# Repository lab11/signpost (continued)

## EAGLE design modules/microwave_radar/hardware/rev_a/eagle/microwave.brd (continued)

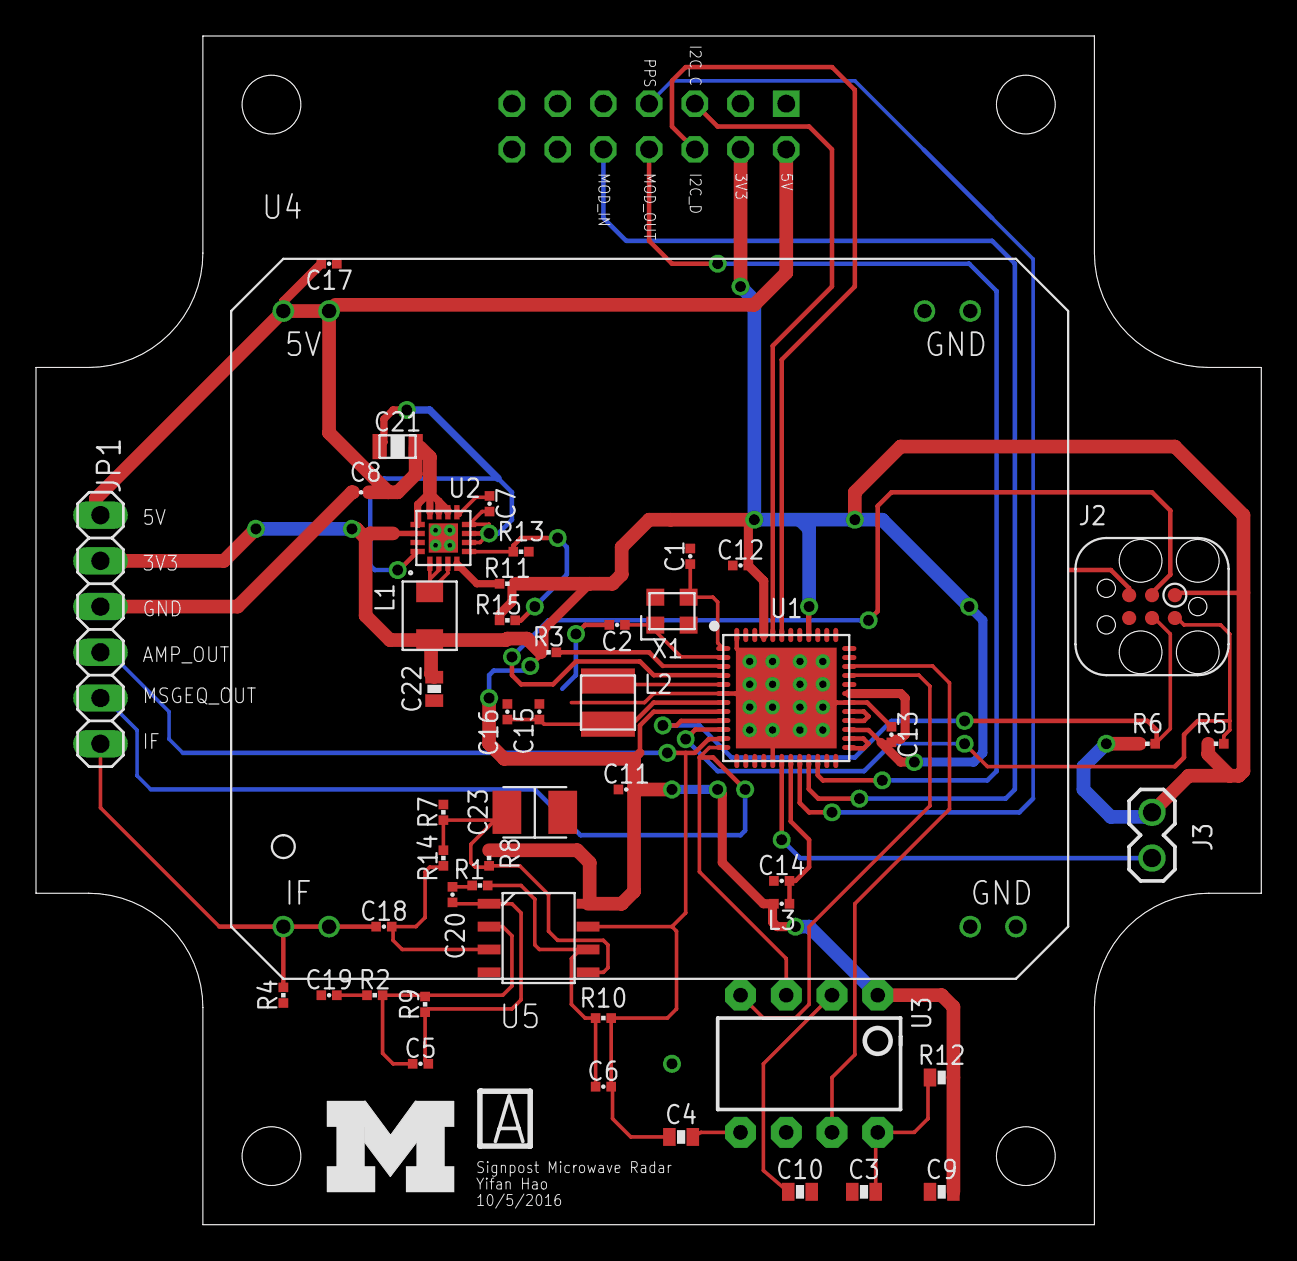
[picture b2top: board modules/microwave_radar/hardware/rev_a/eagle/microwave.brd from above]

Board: 2 copper layers, 68.1 x 66.0 mm, 52 parts (0 on the bottom side), 39 nets.

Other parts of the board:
U$1: UMICH_SOLID_200MIL

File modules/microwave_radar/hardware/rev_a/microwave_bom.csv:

"Qty";"Value";"Device";"Package";"Parts";"Description";"DIGIKEY";
"1";"";"FH1600015";"FHXXX";"X1";"Pericom Type FH 16 MHz 2.5 x 2.0 mm";"FH1600015CT-ND";
"1";"";"JUMPER-2PTH";"1X02";"J3";"Jumper";"";
"1";"";"PINHD-1X8";"1X08";"JP2";"PIN HEADER";"";
"1";"0.1uF";"CAPACITOR0402_CAP";"0402_CAP";"C8";"0402 Capacitor";"490-5920-1-ND";
"2";"0.1uF";"CAPACITOR0603_CAP";"0603_CAP";"C9, C10";"0402 Capacitor";"490-1532-1-ND";
"1";"1.5k";"FERRITE_BEAD0402";"0402_CAP";"L3";"";"490-5216-1-ND";
"6";"100k";"RESISTOR0402_RES";"0402_RES";"R7, R8, R9, R10, R11, R12";"Resistor";"1276-3432-1-ND";
"1";"100k";"RESISTOR0402_RES";"0402_RES";"R13";"Resistor";"P100KJCT-ND";
"6";"100nF";"CAPACITOR0402_CAP";"0402_CAP";"C11, C12, C13, C14, C16, C17";"0402 Capacitor";"490-10777-1-ND";
"1";"100nF";"CAPACITOR0402_CAP";"0402_CAP";"C15";"0402 Capacitor";"490-13252-1-ND";
"1";"100uF";"CAPACITOR1210_CAP";"1210_CAP";"C23";"0402 Capacitor";"490-3390-1-ND";
"2";"10k";"RESISTOR0402_RES";"0402_RES";"R4, R5";"Resistor";"1276-3431-1-ND";
"1";"10uF";"CAPACITOR0805_CAP";"0805_CAP";"C21";"0402 Capacitor";"490-5523-1-ND";
"1";"12k";"RESISTOR0402_RES";"0402_RES";"R6";"Resistor";"1276-4122-1-ND";
"2";"1k";"RESISTOR0402_RES";"0402_RES";"R1, R2";"Resistor";"1276-3430-1-ND";
"1";"1nF";"CAPACITOR0603_CAP";"0603_CAP";"C4";"0402 Capacitor";"490-1494-1-ND";
"2";"2.2nF";"CAPACITOR0402_CAP";"0402_CAP";"C5, C6";"0402 Capacitor";"490-11418-1-ND";
"1";"2.2uH";"INDUCTORIHL";"IHL-1212BZ-11";"L1";"A very specific inductor";"541-1322-1-ND";
"1";"200k";"RESISTOR0603_RES";"0603-RES";"R14";"Resistor";"RHM200KCFCT-ND";
"1";"22uF";"CAPACITOR0603_CAP";"0603_CAP";"C22";"0402 Capacitor";"1276-1193-1-ND";
"1";"22uH";"LHQ3NP";"1212";"L2";"LHQ3NP Inductor";"490-5350-1-ND";
"1";"240k";"RESISTOR0402_RES";"0402_RES";"R15";"Resistor";"P240KLCT-ND";
"1";"3.3nF";"CAPACITOR0402_CAP";"0402_CAP";"C7";"0402 Capacitor";"490-3248-1-ND";
"1";"330k";"RESISTOR0402_RES";"0402_RES";"R16";"Resistor";"1276-4244-1-ND";
"1";"33pF";"CAPACITOR0603_CAP";"0603_CAP";"C3";"0402 Capacitor";"490-1415-1-ND";
"3";"4.7uF";"CAPACITOR0402_CAP";"0402_CAP";"C18, C19, C20";"0402 Capacitor";"1276-1481-1-ND";
"1";"750k";"RESISTOR0402_RES";"0402_RES";"R17";"Resistor";"P750KLCT-ND";
"1";"8.2k";"RESISTOR0402_RES";"0402_RES";"R3";"Resistor";"311-8.20KLRCT-ND";
"2";"8pF";"CAPACITOR0402_CAP";"0402_CAP";"C1, C2";"0402 Capacitor";"490-8230-1-ND";
"1";"HB100";"HB100";"HB100";"U4";"";"SAM1067-02-ND";
"2";"LED0603";"LED0603";"LED-0603";"LED1, LED2";"LED";"";
"1";"MODULE_GENERIC";"MODULE_GENERIC";"MODULE_GENERIC";"J1";"Module header and PCB  guildes for signposts";"S9170-ND";
"1";"MSGEQ7";"MSGEQ7";"DIP-8";"U3";"A CMOS spectrum analyzer";"1568-1335-ND";
"1";"OP284E_SEPARATE";"OP284E_SEPARATE";"OP284E_SEPARATE";"U5";"";"OP284ESZ-ND";
"1";"SAM4LC8AA";"SAM4LC8AA";"QFN-48-7MM";"U1";"Atmel SAM4L microcontroller. ARM Cortex M4 with 512 KB Flash and 64 KB RAM";"ATSAM4LC8AA-MU-ND";
"1";"TC2030-JLINK-L";"TC2030-JLINK-L";"TC2030-IDC";"J2";"";"";
"1";"TLV62130";"TLV62130";"TQFN-16/3MM";"U2";"High Efficient 3A switching step-down regulator. 1V-5V out, 4V-17V in.";"296-35978-1-ND";

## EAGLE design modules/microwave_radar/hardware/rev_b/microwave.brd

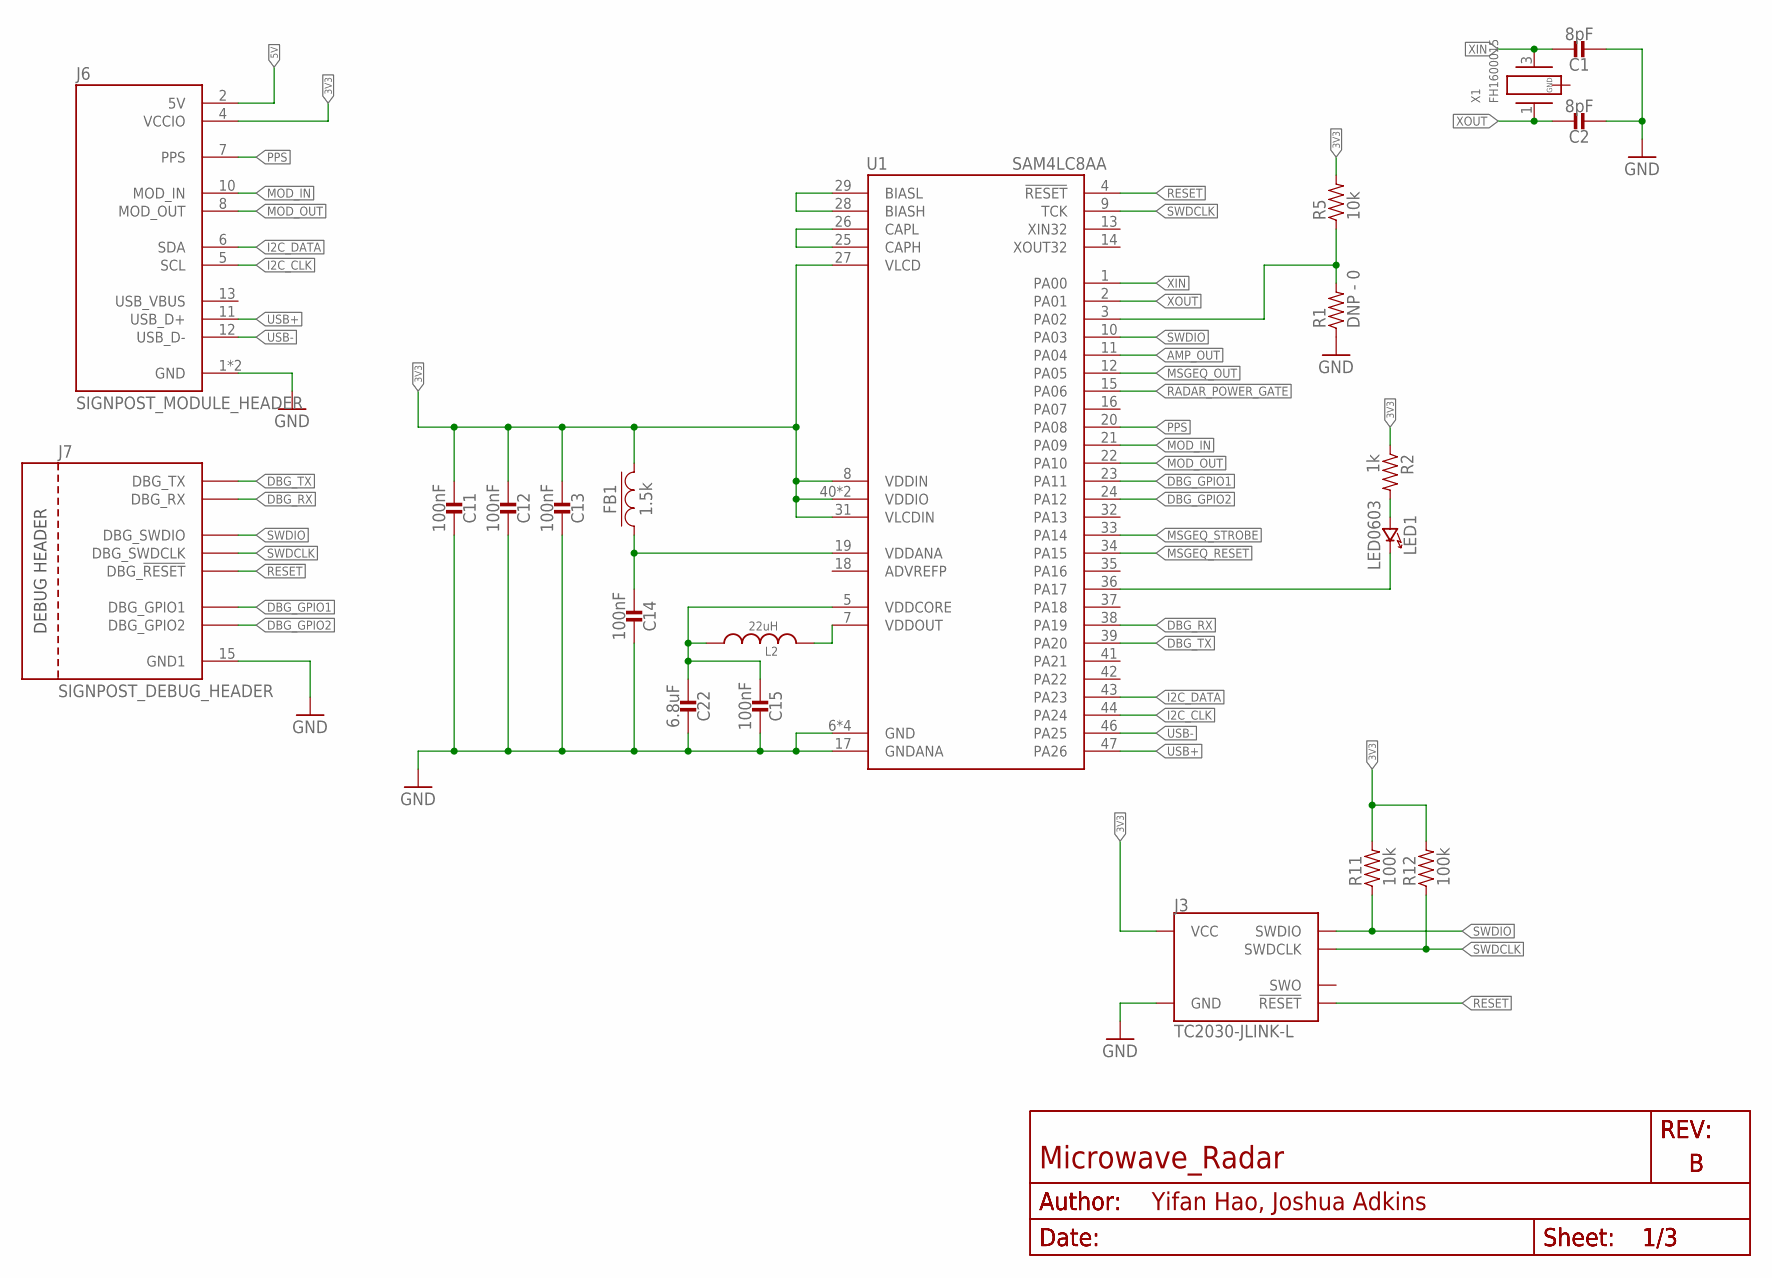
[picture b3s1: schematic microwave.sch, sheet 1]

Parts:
C1, C2: 8pF; 0402_CAP; MPN GRM1555C1H8R0BA01D; DIGIKEY 490-8230-1-ND
C11, C12, C13, C14, C15: 100nF; 0402_CAP; MPN GRM155R71A104JA01D; DIGIKEY 490-10777-1-ND
C22: 6.8uF; 0603_CAP; MPN C1608X5R1A685K080AC; DIGIKEY 445-7484-1-ND
FB1: 1.5k; 0402_CAP; MPN BLM18HE152SN1D; DIGIKEY 490-5216-1-ND
J3: TC2030-JLINK-L; TC2030-IDC
J6: SIGNPOST_MODULE_HEADER
J7: SIGNPOST_DEBUG_HEADER
L2: 22uH; 1212
LED1: LED0603; LED-0603; MPN LTST-C191KGKT; DIGIKEY 160-1446-1-ND
R1: DNP - 0; 0402_RES; MPN RC0402JR-070RL; DIGIKEY 311-0.0JRCT-ND
R2: 1k; 0402_RES; MPN RC1005F102CS; DIGIKEY 1276-3430-1-ND
R5: 10k; 0402_RES; MPN RC1005F103CS; DIGIKEY 1276-3431-1-ND
R11, R12: 100k; 0402_RES; MPN RC1005F104CS; DIGIKEY 1276-3432-1-ND
U1: SAM4LC8AA; QFN-48-7MM
X1: FH1600015; FHXXX

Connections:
3V3: C11.2, C12.2, C13.2, FB1.2, J3.1 (VCC), J6.4 (VCCIO), R2.1, R5.2, R11.2, R12.2, U1.8 (VDDIN), U1.27 (VLCD), U1.31 (VLCDIN), U1.40 (VDDIO), U1.45 (VDDIO); also elsewhere on the board
5V: J6.2 (5V); also elsewhere on the board
!RESET: J3.3 (!RESET), J7.20 (DBG_!RESET), U1.4 (!RESET)
AMP_OUT: U1.11 (PA04); also elsewhere on the board
DBG_GPIO1: J7.16 (DBG_GPIO1), U1.23 (PA11)
DBG_GPIO2: J7.19 (DBG_GPIO2), U1.24 (PA12)
DBG_RX: J7.18 (DBG_RX), U1.38 (PA19); also elsewhere on the board
DBG_TX: J7.17 (DBG_TX), U1.39 (PA20); also elsewhere on the board
GND: C1.2, C2.2, C11.1, C12.1, C13.1, C14.1, C15.1, C22.1, J3.5 (GND), J6.1 (GND), J6.14 (GND), J7.15 (GND1), R1.1, U1.6 (GND), U1.17 (GNDANA), U1.30 (GND), U1.48 (GND), U1.THERMAL (GND); also elsewhere on the board
I2C_CLK: J6.5 (SCL), U1.44 (PA24)
I2C_DATA: J6.6 (SDA), U1.43 (PA23)
MOD_IN: J6.10 (MOD_IN), U1.21 (PA09)
MOD_OUT: J6.8 (MOD_OUT), U1.22 (PA10)
MSGEQ_OUT: U1.12 (PA05); also elsewhere on the board
MSGEQ_RESET: U1.34 (PA15); also elsewhere on the board
MSGEQ_STROBE: U1.33 (PA14); also elsewhere on the board
unnamed: L2.P$2 (2), U1.7 (VDDOUT)
unnamed: U1.28 (BIASH), U1.29 (BIASL)
unnamed: U1.25 (CAPH), U1.26 (CAPL)
unnamed: C14.2, FB1.1, U1.19 (VDDANA)
unnamed: R1.2, R5.1, U1.3 (PA02)
unnamed: LED1.A (ANODE), R2.2
unnamed: LED1.C (CATHODE), U1.36 (PA17)
unnamed: C15.2, C22.2, L2.P$1 (1), U1.5 (VDDCORE)
PPS: J6.7 (PPS), U1.20 (PA08)
RADAR_POWER_GATE: U1.15 (PA06); also elsewhere on the board
SWDCLK: J3.4 (SWDCLK), J7.21 (DBG_SWDCLK), R12.1, U1.9 (TCK)
SWDIO: J3.2 (SWDIO), J7.22 (DBG_SWDIO), R11.1, U1.10 (PA03)
USB+: J6.11 (USB_D+), U1.47 (PA26)
USB-: J6.12 (USB_D-), U1.46 (PA25)
XIN: C1.1, U1.1 (PA00), X1.3 (2)
XOUT: C2.1, U1.2 (PA01), X1.1

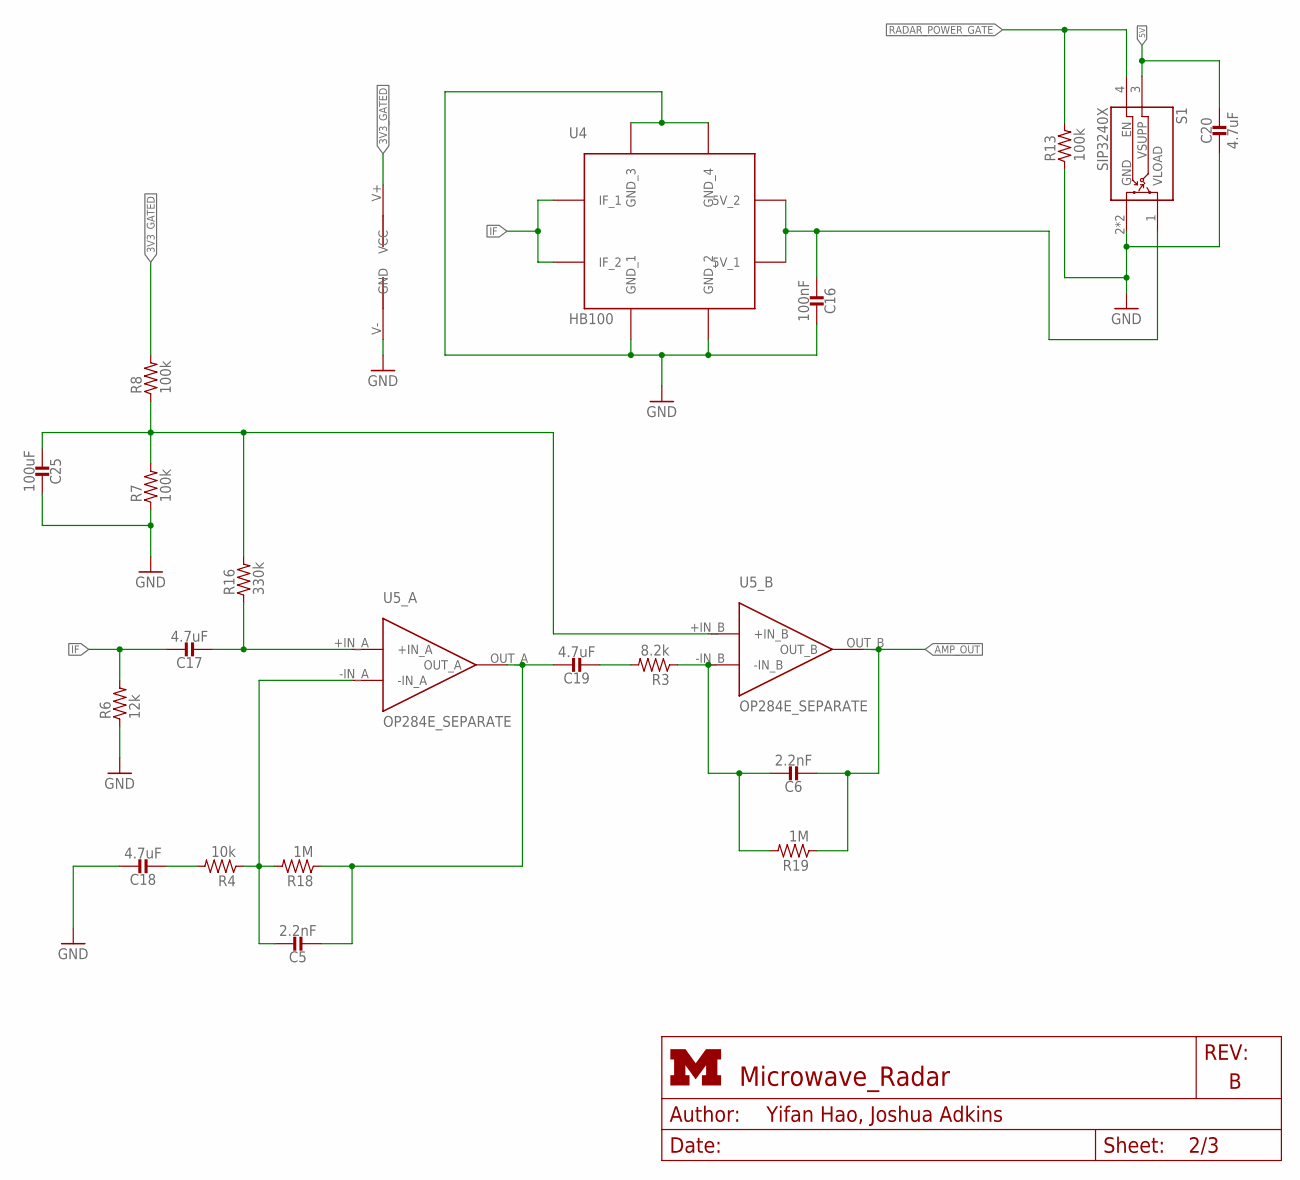
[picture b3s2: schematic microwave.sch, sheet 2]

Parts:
C5, C6: 2.2nF; 0402_CAP; MPN GRM155R70J222KA01D; DIGIKEY 490-11418-1-ND
C16: 100nF; 0402_CAP; MPN GRM155R71A104JA01D; DIGIKEY 490-10777-1-ND
C17, C18, C19, C20: 4.7uF; 0402_CAP; MPN CL05A475KQ5NRNC; DIGIKEY 1276-1481-1-ND
C25: 100uF; 1210_CAP; MPN GRM32ER60J107ME20L; DIGIKEY 490-3390-1-ND
R3: 8.2k; 0402_RES; MPN RC0402FR-078K2L; DIGIKEY 311-8.20KLRCT-ND
R4: 10k; 0402_RES; MPN RC1005F103CS; DIGIKEY 1276-3431-1-ND
R6: 12k; 0402_RES; MPN RC1005F123CS; DIGIKEY 1276-4122-1-ND
R7, R8, R13: 100k; 0402_RES; MPN RC1005F104CS; DIGIKEY 1276-3432-1-ND
R16: 330k; 0402_RES; MPN RC1005F334CS; DIGIKEY 1276-4244-1-ND
R18, R19: 1M; 0402_RES; MPN RC1005F104CS; DIGIKEY 1276-3432-1-ND
S1: SIP3240X; TDFN4
U4: HB100; MPN TSW-102-17-T-S; DIGIKEY SAM1067-02-ND
U5: OP284E_SEPARATE; MPN OP284ESZ; DIGIKEY OP284ESZ-ND

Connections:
3V3_GATED: R8.2, U5.V+ (VCC); also elsewhere on the board
5V: C20.1, S1.3 (VSUPP); also elsewhere on the board
5V_GATED: C16.2, S1.1 (VLOAD), U4.5V_1, U4.5V_2
AMP_OUT: C6.2, R19.1, U5.OUT_B; also elsewhere on the board
GND: C16.1, C18.1, C20.2, C25.1, R6.1, R7.1, R13.1, S1.2 (GND), S1.PAD (GND), U4.GND_1, U4.GND_2, U4.GND_3, U4.GND_4, U5.V- (GND); also elsewhere on the board
IF: C17.1, R6.2, U4.IF_1, U4.IF_2; also elsewhere on the board
unnamed: C25.2, R7.2, R8.1, R16.2, U5.+IN_B
unnamed: C17.2, R16.1, U5.+IN_A
unnamed: C5.1, R4.1, R18.2, U5.-IN_A
unnamed: C18.2, R4.2
unnamed: C5.2, C19.1, R18.1, U5.OUT_A
unnamed: C19.2, R3.2
unnamed: C6.1, R3.1, R19.2, U5.-IN_B
RADAR_POWER_GATE: R13.2, S1.4 (EN); also elsewhere on the board

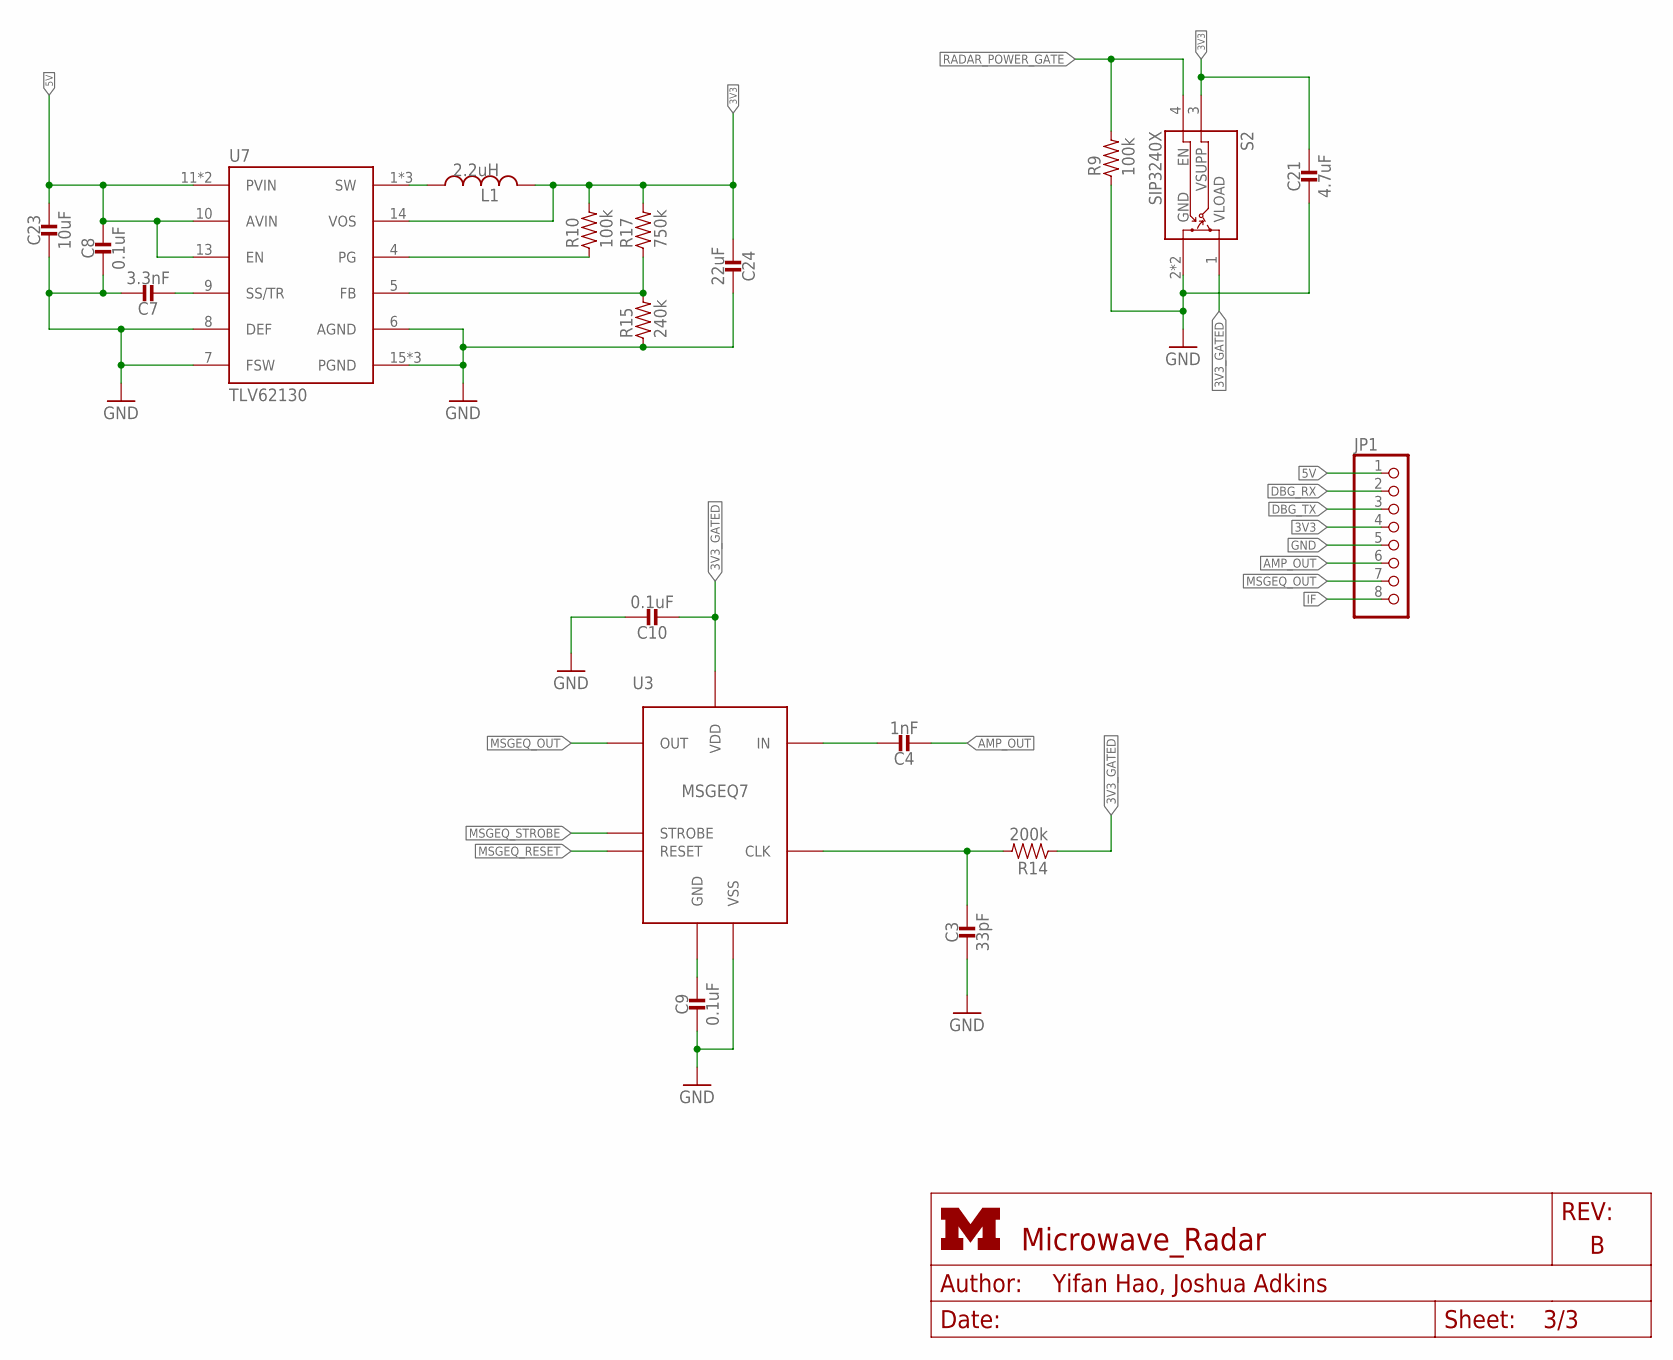
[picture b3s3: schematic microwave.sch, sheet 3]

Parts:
C3: 33pF; 0603_CAP; MPN GRM1885C1H330JA01D; DIGIKEY 490-1415-1-ND
C4: 1nF; 0603_CAP; MPN GRM188R71H102KA01D; DIGIKEY 490-1494-1-ND
C7: 3.3nF; 0402_CAP; MPN GRM155R71H332KA01D; DIGIKEY 490-3248-1-ND
C8: 0.1uF; 0402_CAP; MPN GRM155R71C104KA88J; DIGIKEY 490-6328-1-ND
C9, C10: 0.1uF; 0603_CAP; MPN GRM188R71C104KA01D; DIGIKEY 490-1532-1-ND
C21: 4.7uF; 0402_CAP; MPN CL05A475KQ5NRNC; DIGIKEY 1276-1481-1-ND
C23: 10uF; 0805_CAP; MPN C0805C106K8PACTU; DIGIKEY 399-4925-1-ND
C24: 22uF; 0603_CAP; MPN CC0603MRX5R5BB226; DIGIKEY 311-1815-1-ND
JP1: PINHD-1X8; 1X08
L1: 2.2uH; IHL-1212BZ-11
R9, R10: 100k; 0402_RES; MPN RC1005F104CS; DIGIKEY 1276-3432-1-ND
R14: 200k; 0603-RES; MPN RC0603JR-07200KL; DIGIKEY 311-200KGRCT-ND
R15: 240k; 0402_RES; MPN ERJ-2RKF2403X; DIGIKEY P240KLCT-ND
R17: 750k; 0402_RES; MPN ERJ-2RKF7503X; DIGIKEY P750KLCT-ND
S2: SIP3240X; TDFN4
U3: MSGEQ7; DIP-8
U7: TLV62130; TQFN-16/3MM

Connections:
3V3: C21.1, C24.2, JP1.4, L1.P$2 (2), R10.2, R17.2, S2.3 (VSUPP), U7.14 (VOS); also elsewhere on the board
3V3_GATED: C10.2, R14.1, S2.1 (VLOAD), U3.1 (VDD); also elsewhere on the board
5V: C8.1, C23.P$1 (1), JP1.1, U7.10 (AVIN), U7.11 (PVIN), U7.12 (PVIN), U7.13 (EN); also elsewhere on the board
AMP_OUT: C4.2, JP1.6; also elsewhere on the board
DBG_RX: JP1.2; also elsewhere on the board
DBG_TX: JP1.3; also elsewhere on the board
GND: C3.2, C7.1, C8.2, C9.2, C10.1, C21.2, C23.P$2 (2), C24.1, JP1.5, R9.1, R15.1, S2.2 (GND), S2.PAD (GND), U3.2 (VSS), U7.6 (AGND), U7.7 (FSW), U7.8 (DEF), U7.15 (PGND), U7.16 (PGND), U7.GND; also elsewhere on the board
IF: JP1.8; also elsewhere on the board
MSGEQ_OUT: JP1.7, U3.3 (OUT); also elsewhere on the board
MSGEQ_RESET: U3.7 (RESET); also elsewhere on the board
MSGEQ_STROBE: U3.4 (STROBE); also elsewhere on the board
unnamed: C3.1, R14.2, U3.8 (CLK)
unnamed: C4.1, U3.5 (IN)
unnamed: C9.1, U3.6 (GND)
unnamed: C7.2, U7.9 (SS/TR)
unnamed: L1.P$1 (1), U7.1 (SW), U7.2 (SW), U7.3 (SW)
unnamed: R10.1, U7.4 (PG)
unnamed: R15.2, R17.1, U7.5 (FB)
RADAR_POWER_GATE: R9.2, S2.4 (EN); also elsewhere on the board

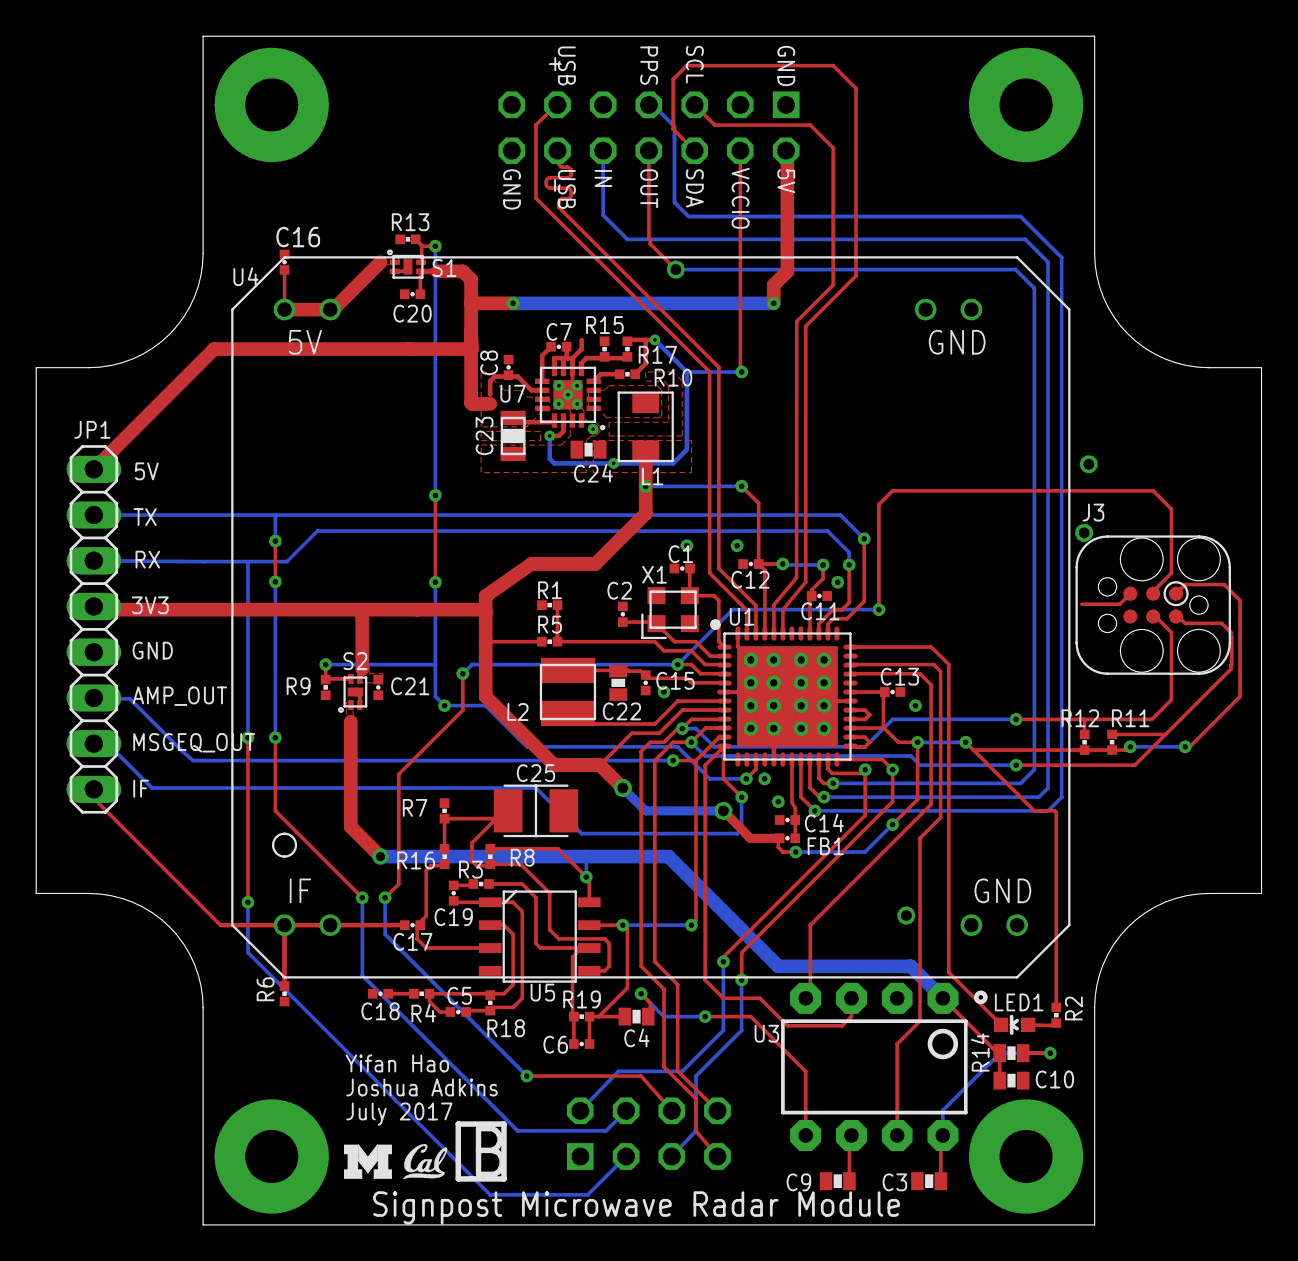
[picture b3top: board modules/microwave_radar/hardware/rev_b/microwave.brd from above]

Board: 2 copper layers, 68.1 x 66.0 mm, 62 parts (0 on the bottom side), 49 nets.

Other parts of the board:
U$2: UMICH_SOLID_75MIL
U$3: UCB_CAL_75MIL

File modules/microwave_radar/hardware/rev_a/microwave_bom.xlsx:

Qty | Value | Device | Package | Parts | Description | DIGIKEY |  | Get from controller
2 | 8pF | CAPACITOR0402_CAP | 0402_CAP | C1, C2 | 0402 Capacitor | 490-8230-1-ND |  | yes
6 | 100nF | CAPACITOR0402_CAP | 0402_CAP | C11, C12, C13, C14, C16, C17 | 0402 Capacitor | 490-10777-1-ND |  | yes
1 | 100nF | CAPACITOR0402_CAP | 0402_CAP | C15 | 0402 Capacitor | 490-13252-1-ND
3 | 4.7uF | CAPACITOR0402_CAP | 0402_CAP | C18, C19, C20 | 0402 Capacitor | 1276-1481-1-ND
1 | 10uF | CAPACITOR0805_CAP | 0805_CAP | C21 | 0402 Capacitor | 490-5523-1-ND |  |  | Out of stock: Substituting 1276-2891-1-ND
1 | 22uF | CAPACITOR0603_CAP | 0603_CAP | C22 | 0402 Capacitor | 1276-1193-1-ND
1 | 100uF | CAPACITOR1210_CAP | 1210_CAP | C23 | 0402 Capacitor | 490-3390-1-ND
1 | 33pF | CAPACITOR0603_CAP | 0603_CAP | C3 | 0402 Capacitor | 490-1415-1-ND
1 | 1nF | CAPACITOR0603_CAP | 0603_CAP | C4 | 0402 Capacitor | 490-1494-1-ND
2 | 2.2nF | CAPACITOR0402_CAP | 0402_CAP | C5, C6 | 0402 Capacitor | 490-11418-1-ND
1 | 3.3nF | CAPACITOR0402_CAP | 0402_CAP | C7 | 0402 Capacitor | 490-3248-1-ND
1 | 0.1uF | CAPACITOR0402_CAP | 0402_CAP | C8 | 0402 Capacitor | 490-5920-1-ND
2 | 0.1uF | CAPACITOR0603_CAP | 0603_CAP | C9, C10 | 0402 Capacitor | 490-1532-1-ND
1 | MODULE_GENERIC | MODULE_GENERIC | MODULE_GENERIC | J1 | Module header and PCB guildes for signposts | S9170-ND |  | yes
1 | TC2030-JLINK-L | TC2030-JLINK-L | TC2030-IDC | J2
1 |  | JUMPER-2PTH | 1X02 | J3 | Jumper |  |  | yes
1 |  | PINHD-1X8 | 1X08 | JP2 | PIN HEADER |  |  | yes
1 | 2.2uH | INDUCTORIHL | IHL-1212BZ-11 | L1 | A very specific inductor | 541-1322-1-ND
1 | 22uH | LHQ3NP | 1212 | L2 | LHQ3NP Inductor | 490-5350-1-ND |  | yes
1 | 1.5k | FERRITE_BEAD0402 | 0402_CAP | L3 |  | 490-5216-1-ND |  | yes
2 | LED0603 | LED0603 | LED-0603 | LED1, LED2 | LED |  |  | yes
2 | 1k | RESISTOR0402_RES | 0402_RES | R1, R2 | Resistor | 1276-3430-1-ND |  | yes
1 | 100k | RESISTOR0402_RES | 0402_RES | R13 | Resistor | P100KJCT-ND
1 | 200k | RESISTOR0603_RES | 0603-RES | R14 | Resistor | RHM200KCFCT-ND
1 | 240k | RESISTOR0402_RES | 0402_RES | R15 | Resistor | P240KLCT-ND
1 | 330k | RESISTOR0402_RES | 0402_RES | R16 | Resistor | 1276-4244-1-ND
1 | 750k | RESISTOR0402_RES | 0402_RES | R17 | Resistor | P750KLCT-ND
1 | 8.2k | RESISTOR0402_RES | 0402_RES | R3 | Resistor | 311-8.20KLRCT-ND
2 | 10k | RESISTOR0402_RES | 0402_RES | R4, R5 | Resistor | 1276-3431-1-ND |  | yes
1 | 12k | RESISTOR0402_RES | 0402_RES | R6 | Resistor | 1276-4122-1-ND
6 | 100k | RESISTOR0402_RES | 0402_RES | R7, R8, R9, R10, R11, R12 | Resistor | 1276-3432-1-ND |  | yes
1 | SAM4LC8AA | SAM4LC8AA | QFN-48-7MM | U1 | Atmel SAM4L microcontroller. ARM Cortex M4 with 512 KB Flash and 64 KB RAM | ATSAM4LC8AA-MU-ND |  | yes
1 | TLV62130 | TLV62130 | TQFN-16/3MM | U2 | High Efficient 3A switching step-down regulator. 1V-5V out, 4V-17V in. | 296-35978-1-ND
1 | MSGEQ7 | MSGEQ7 | DIP-8 | U3 | A CMOS spectrum analyzer | 1568-1335-ND
1 | HB100 | HB100 | HB100 | U4 |  | SAM1067-02-ND |  | ordered from amazon
1 | OP284E_SEPARATE | OP284E_SEPARATE | OP284E_SEPARATE | U5 |  | OP284ESZ-ND
1 |  | FH1600015 | FHXXX | X1 | Pericom Type FH 16 MHz 2.5 x 2.0 mm | FH1600015CT-ND |  | yes

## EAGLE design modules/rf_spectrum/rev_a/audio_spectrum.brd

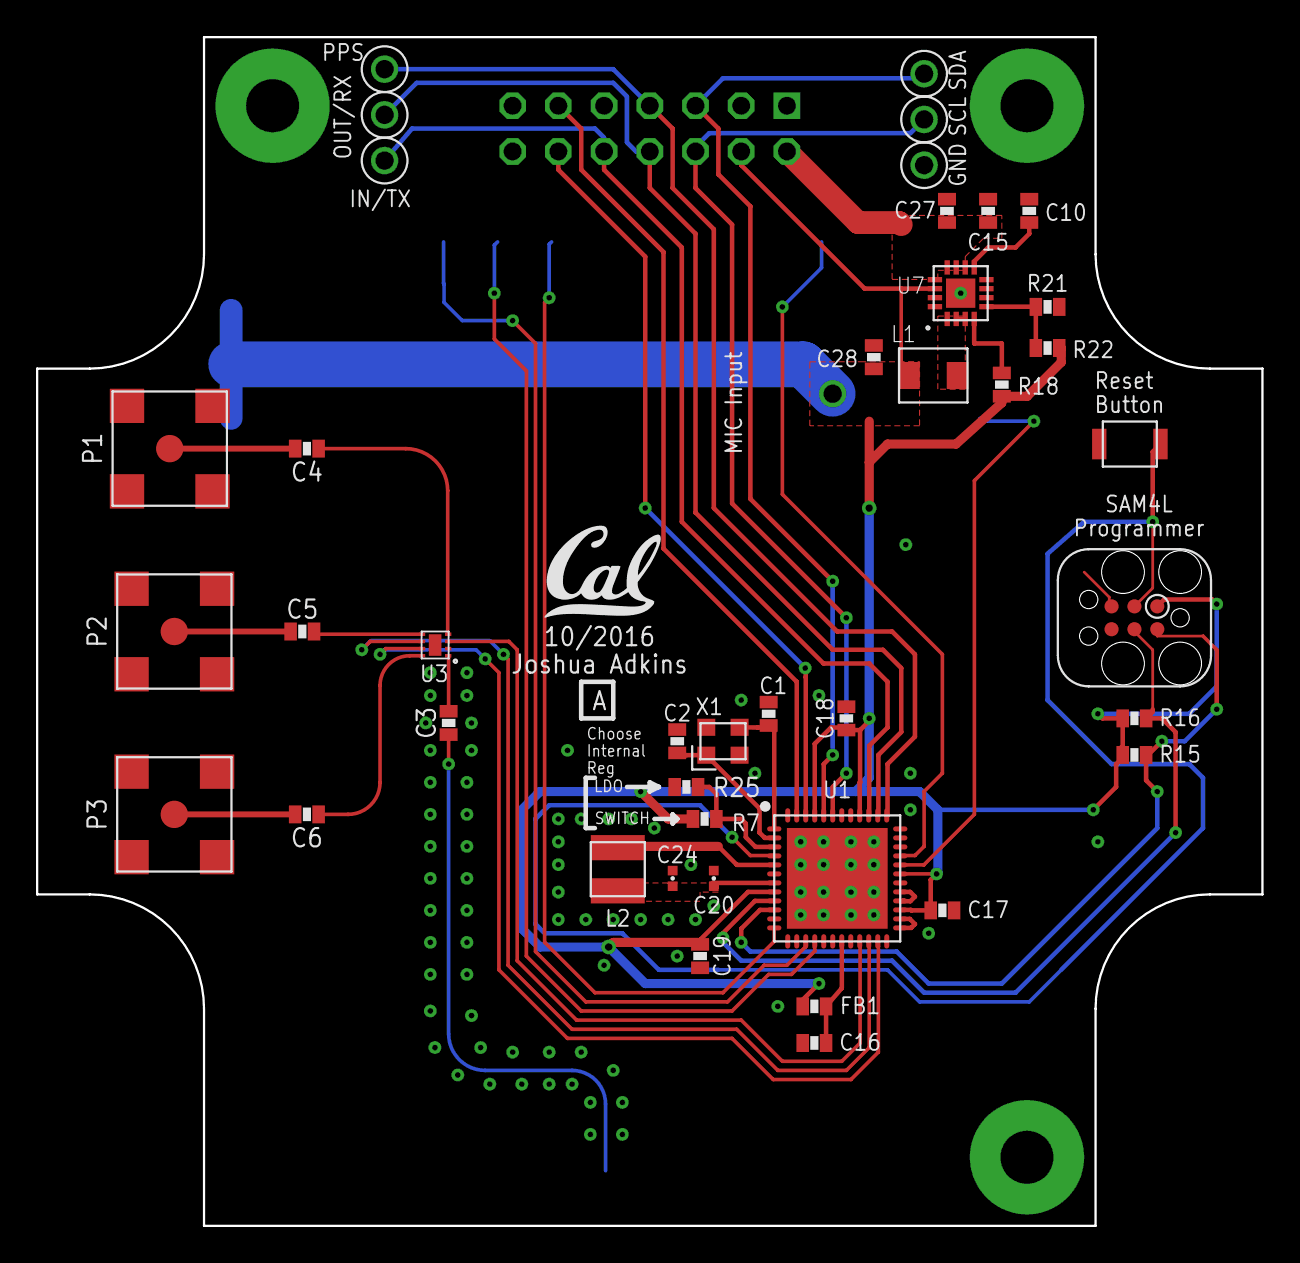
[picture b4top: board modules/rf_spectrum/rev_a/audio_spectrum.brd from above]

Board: 2 copper layers, 68.1 x 66.0 mm, 44 parts (1 on the bottom side), 41 nets.

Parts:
C1, C2: 8pF; 0603_CAP
C3, C5, C6: 47pF; 0603_CAP
C4: 220pF; 0603_CAP
C10: 3.3nF; 0603_CAP
C15: 0.1uF; 0603_CAP
C16, C17, C18, C19: 100nF; 0603_CAP
C20: 100nF; 0402_CAP
C24: 4.7uF; 0402_CAP
C27: 10uF; 0603_CAP
C28: 22uF; 0603_CAP
FB1: 1.5kΩ; 0603_CAP
J1: MODULE_GENERIC
J7: TC2030-JLINK-L; TC2030-IDC
L1: 2.2uH; IHL-1212BZ-11
L2: 22uH; 1212
P1, P2, P3: MOLEX_73251-135X; SMA-J/PCB
R7: 10k; 0603-RES
R15, R16, R18: 100k; 0603-RES
R21: 240k; 0603-RES
R22: 750k; 0603-RES
R25: 0; 0603-RES
S1: B3U-1000P
TP11, TP12, TP13, TP14, TP15, TP16: TEST_POINT_0.040IN; TESTPOINT_0.040IN
U1: SAM4LC8AA; QFN-48-7MM
U2: MWSUB3G
U3: SKY13317; XDFN-8
U7: TLV62130; TQFN-16/3MM
U$2: UCB_CAL_200MIL
X1: 16MHz; FHXXX

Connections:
3V3: C17.1, C18.1, C19.1, C28.2, FB1.2, J1.4, J7.1, L1.P$2, R7.2, R15.2, R16.2, R18.2, R22.2, U1.8, U1.27, U1.31, U1.40, U1.45, U2.P$31, U2.P$32, U2.P$33, U7.14
3VSWOUT: L1.P$1, U7.1, U7.2, U7.3
5V: C15.1, C27.1, J1.2, U7.10, U7.11, U7.12, U7.13
!CONTROLLER_RESET: J7.3, S1.2, U1.4
CONTROLLER_BUCK/LDO_N: R7.1, R25.2, U1.3
CONTROLLER_SWDCLK: J7.4, R16.1, U1.9
CONTROLLER_SWDIO: J7.2, R15.1, U1.10
CONTROLLER_XIN: C1.1, U1.1, X1.3
CONTROLLER_XOUT: C2.1, U1.2, X1.1
GND: C1.2, C2.2, C10.1, C15.2, C16.2, C17.2, C18.2, C19.2, C20.2, C24.2, C27.2, C28.1, J1.1, J1.14, J7.5, P1.2, P1.3, P1.4, P1.5, P2.2, P2.3, P2.4, P2.5, P3.2, P3.3, P3.4, P3.5, R21.1, R25.1, S1.1, TP11.TESTPOINT, U1.6, U1.17, U1.30, U1.48, U1.THERMAL, U2.P$5, U2.P$6, U2.P$7, U2.P$8, U2.P$9, U2.P$10, U2.P$11, U2.P$12, U2.P$13, U2.P$14, U2.P$15, U2.P$16, U2.P$18, U2.P$20, U2.P$21, U2.P$22, U2.P$24, U2.P$26, U2.P$27, U2.P$28, U2.P$29, U2.P$34, U2.P$43, U2.P$45, U2.P$46, U3.P$1, U7.6, U7.7, U7.8, U7.15, U7.16, U7.GND, X1.2, X1.4
MOD_IN: J1.10, TP14.TESTPOINT, U1.39
MOD_OUT: J1.8, TP15.TESTPOINT, U1.38
unnamed: C3.1, U2.P$17
unnamed: C3.2, U3.1
unnamed: C4.1, U3.4
unnamed: C4.2, P1.1
unnamed: C5.2, U3.5
unnamed: C5.1, P2.1
unnamed: C6.1, U3.8
unnamed: C6.2, P3.1
unnamed: C16.1, FB1.1, U1.19
unnamed: C10.2, U7.9
unnamed: R18.1, U7.4
unnamed: R21.2, R22.1, U7.5
unnamed: C20.1, C24.1, L2.P$1, U1.7
unnamed: L2.P$2, U1.5
unnamed: U1.28, U1.29
unnamed: U1.25, U1.26
PPS: J1.7, TP16.TESTPOINT, U1.37
RF_ANT1: U1.21, U3.3
RF_ANT2: U1.22, U3.6
RF_ANT3: U1.23, U3.7
RF_GPIO2: U1.32, U2.P$3
RF_GPIO3: U1.15, U2.P$37
RF_RESET: U1.33, U2.P$44
RF_RX: U1.16, U2.P$38
RF_TX: U1.12, U2.P$39
SCL: J1.5, TP12.TESTPOINT, U1.44
SDA: J1.6, TP13.TESTPOINT, U1.43
USB+: J1.11, U1.47
USB-: J1.12, U1.46
